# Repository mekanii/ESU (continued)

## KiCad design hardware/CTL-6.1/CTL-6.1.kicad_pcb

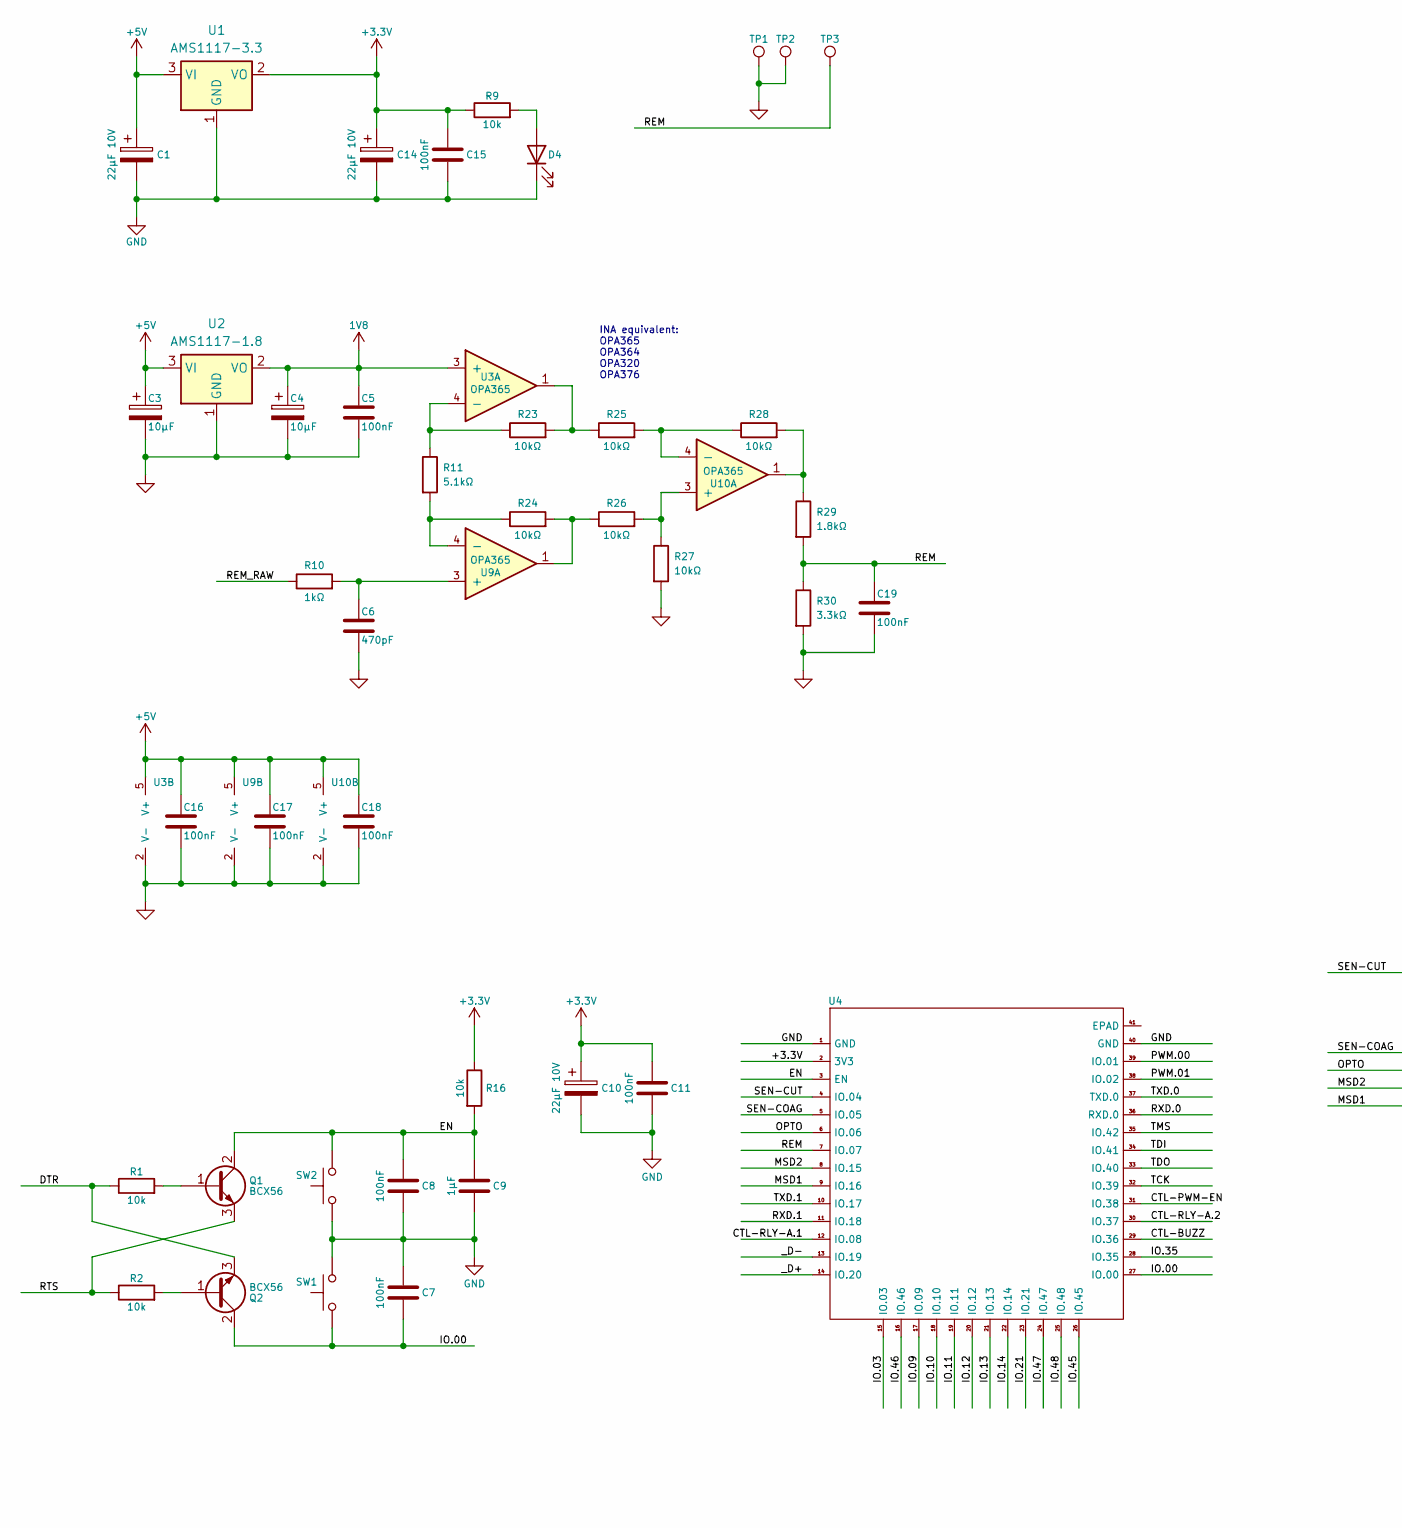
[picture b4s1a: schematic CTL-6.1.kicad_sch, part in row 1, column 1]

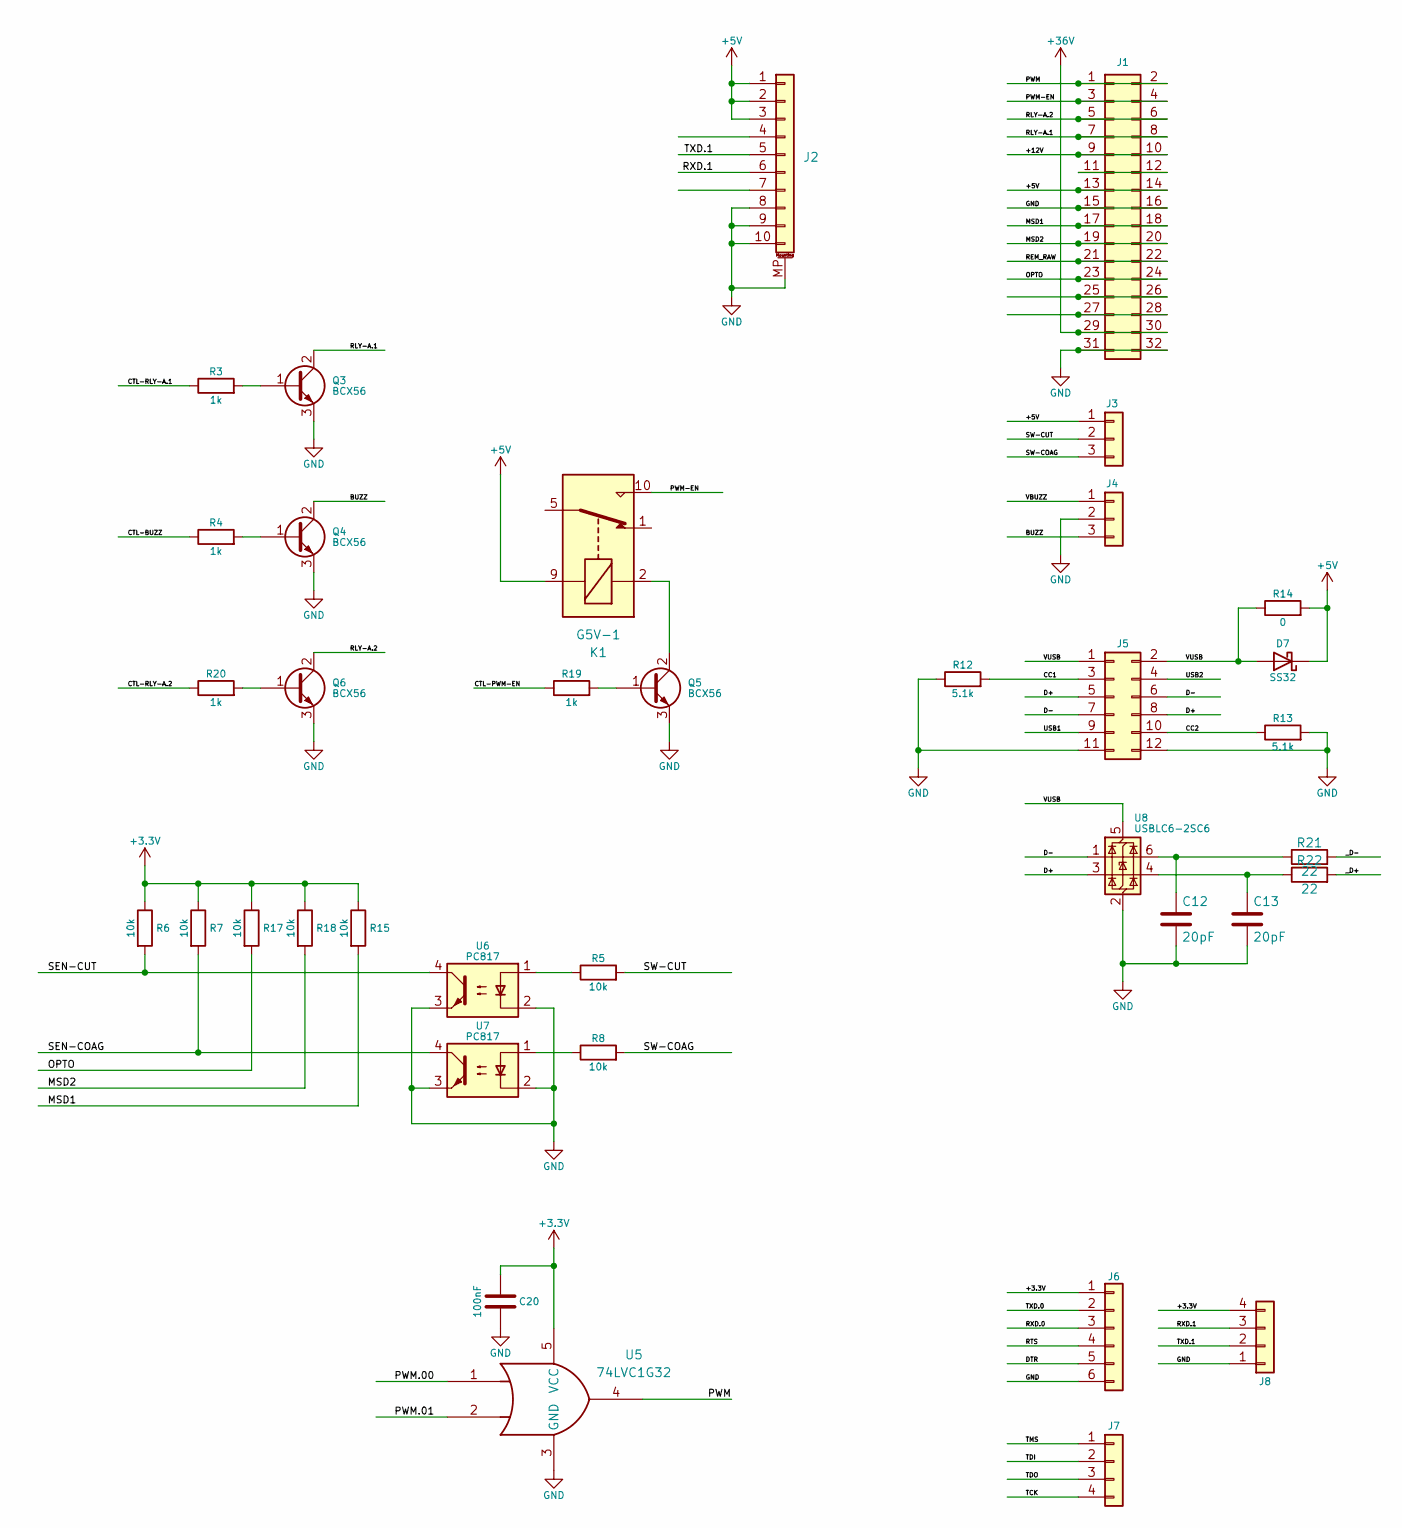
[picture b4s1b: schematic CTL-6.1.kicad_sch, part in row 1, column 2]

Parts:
C1, C10, C14: 22µF 10V; CP_EIA-3216-18_Kemet-A_Pad1.58x1.35mm_HandSolder
C3, C4: 10µF; CP_EIA-3216-18_Kemet-A_Pad1.58x1.35mm_HandSolder
C5, C7, C8, C11, C15, C16, C17, C18, C19, C20: 100nF; C_0805_2012Metric_Pad1.18x1.45mm_HandSolder
C6: 470pF; C_0805_2012Metric_Pad1.18x1.45mm_HandSolder
C9: 1µF; C_0805_2012Metric_Pad1.18x1.45mm_HandSolder
C12, C13: 20pF; C_0805_2012Metric_Pad1.18x1.45mm_HandSolder
D4: LED; LED_0805_2012Metric_Pad1.15x1.40mm_HandSolder
D7: SS32; D_SMA
J1: Conn_02x16_Top_Bottom; PinHeader_2x16_P2.54mm_Horizontal_NoPins
J2: TE_1-84952-0_1x10-1MP_P1.0mm_Horizontal
J3, J4: Conn_01x03; JST_XH_B3B-XH-A_1x03_P2.50mm_Vertical
J5: Conn_02x06_Odd_Even; PinHeader_2x06_P2.54mm_Vertical
J6: Conn_01x04; PinHeader_1x06_P2.54mm_Vertical
J7, J8: Conn_01x04; PinHeader_1x04_P2.54mm_Vertical
K1: G5V-1; Relay_SPDT_Omron_G5V-1
Q1, Q2, Q3, Q4, Q5, Q6: BCX56; SOT-89-3
R1, R2, R5, R6, R7, R8, R9, R15, R16, R17, R18: 10k; R_0805_2012Metric_Pad1.20x1.40mm_HandSolder
R3, R4, R19, R20: 1k; R_0805_2012Metric_Pad1.20x1.40mm_HandSolder
R10: 1kΩ; R_0805_2012Metric_Pad1.20x1.40mm_HandSolder
R11: 5.1kΩ; R_0805_2012Metric_Pad1.20x1.40mm_HandSolder
R12, R13: 5.1k; R_0805_2012Metric_Pad1.20x1.40mm_HandSolder
R14: 0; R_1206_3216Metric_Pad1.30x1.75mm_HandSolder
R21, R22: 22; R_0805_2012Metric_Pad1.20x1.40mm_HandSolder
R23, R24, R25, R26, R27, R28: 10kΩ; R_0805_2012Metric_Pad1.20x1.40mm_HandSolder
R29: 1.8kΩ; R_0805_2012Metric_Pad1.20x1.40mm_HandSolder
R30: 3.3kΩ; R_0805_2012Metric_Pad1.20x1.40mm_HandSolder
SW1, SW2: SW_Omron_B3FS; SW_SPST_Omron_B3FS-100xP
TP1, TP2, TP3: TestPoint; TestPoint_Bridge_Pitch2.54mm_Drill1.0mm
U1: AMS1117-3.3; SOT-223-3_TabPin2
U2: AMS1117-1.8; SOT-223-3_TabPin2
U3, U9, U10: OPA365; SOT-23-5_HandSoldering
U4: ESP32-S3-WROOM-1U
U5: 74LVC1G32; SOT-23-5_HandSoldering
U6, U7: PC817; DIP-4_W7.62mm_Socket
U8: USBLC6-2SC6; SOT-23-6

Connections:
1V8: C4.1, C5.1, U2.2 (VO), U3.3 (+)
+3.3V: C10.1, C11.2, C14.1, C15.2, C20.2, J6.1, J8.4, R6.1, R7.1, R9.1, R15.1, R16.1, R17.1, R18.1, U1.2 (VO), U4.2 (3V3), U5.5 (VCC)
+5V: C1.1, C3.1, C16.1, C17.1, C18.1, D7.1 (K), J1.13, J1.14, J2.1, J2.2, J2.3, J3.1, K1.9, R14.2, U1.3 (VI), U2.3 (VI), U3.5 (V+), U9.5 (V+), U10.5 (V+)
+36V: J1.29, J1.30
/+12V: J1.9, J1.10
/BUZZ: J4.3, Q4.2 (C)
/CC1: J5.3, R12.2
/CC2: J5.10, R13.1
/CTL-BUZZ: R4.1, U4.29 (IO.36)
/CTL-PWM-EN: R19.1, U4.31 (IO.38)
/CTL-RLY-A.1: R3.1, U4.12 (IO.08)
/CTL-RLY-A.2: R20.1, U4.30 (IO.37)
/D+: J5.5, J5.8, U8.3 (I/O2)
/D-: J5.6, J5.7, U8.1 (I/O1)
/DTR: J6.5, Q2.3 (E), R1.1
/EN: C8.2, C9.2, Q1.2 (C), R16.2, SW2.2, U4.3 (EN)
/IO.00: C7.2, Q2.2 (C), SW1.1, U4.27 (IO.00)
/IO.03: U4.15 (IO.03)
/IO.09: U4.17 (IO.09)
/IO.10: U4.18 (IO.10)
/IO.11: U4.19 (IO.11)
/IO.12: U4.20 (IO.12)
/IO.13: U4.21 (IO.13)
/IO.14: U4.22 (IO.14)
/IO.21: U4.23 (IO.21)
/IO.35: U4.28 (IO.35)
/IO.45: U4.26 (IO.45)
/IO.46: U4.16 (IO.46)
/IO.47: U4.24 (IO.47)
/IO.48: U4.25 (IO.48)
/MSD1: J1.17, J1.18, R15.2, U4.9 (IO.16)
/MSD2: J1.19, J1.20, R18.2, U4.8 (IO.15)
/OPTO: J1.23, J1.24, R17.2, U4.6 (IO.06)
/PWM: J1.1, J1.2, U5.4
/PWM-EN: J1.3, J1.4, K1.10
/PWM.00: U4.39 (IO.01), U5.1
/PWM.01: U4.38 (IO.02), U5.2
/REM: C19.1, R29.2, R30.1, TP3.1 (1_1), U4.7 (IO.07)
/REM_RAW: J1.21, J1.22, R10.1
/RLY-A.1: J1.7, J1.8, Q3.2 (C)
/RLY-A.2: J1.5, J1.6, Q6.2 (C)
/RTS: J6.4, Q1.3 (E), R2.1
/RXD.0: J6.3, U4.36 (RXD.0)
/RXD.1: J2.6, J8.3, U4.11 (IO.18)
/SEN-COAG: R7.2, U4.5 (IO.05), U7.4
/SEN-CUT: R6.2, U4.4 (IO.04), U6.4
/SW-COAG: J3.3, R8.2
/SW-CUT: J3.2, R5.2
/TCK: J7.4, U4.32 (IO.39)
/TDI: J7.2, U4.34 (IO.41)
/TDO: J7.3, U4.33 (IO.40)
/TMS: J7.1, U4.35 (IO.42)
/TXD.0: J6.2, U4.37 (TXD.0)
/TXD.1: J2.5, J8.2, U4.10 (IO.17)
/USB1: J5.9
/USB2: J5.4
/VBUZZ: J4.1
/VUSB: D7.2 (A), J5.1, J5.2, R14.1, U8.5 (VBUS)
/_D+: R22.2, U4.14 (IO.20)
/_D-: R21.2, U4.13 (IO.19)
GND: C1.2, C3.2, C4.2, C5.2, C6.2, C7.1, C8.1, C9.1, C10.2, C11.1, C12.2, C13.2, C14.2, C15.1, C16.2, C17.2, C18.2, C19.2, C20.1, D4.1 (K), J1.15, J1.16, J1.31, J1.32, J2.8, J2.9, J2.10, J2.MP (MountPin), J4.2, J5.11, J5.12, J6.6, J8.1, Q3.3 (E), Q4.3 (E), Q5.3 (E), Q6.3 (E), R12.1, R13.2, R27.2, R30.2, SW1.2, SW2.1, TP1.1 (1_1), TP2.1 (1_1), U1.1 (GND), U2.1 (GND), U3.2 (V-), U4.1 (GND), U4.40 (GND), U5.3 (GND), U6.2, U6.3, U7.2, U7.3, U8.2 (GND), U9.2 (V-), U10.2 (V-)
unnamed: C12.1, R21.1, U8.6 (I/O1)
unnamed: C13.1, R22.1, U8.4 (I/O2)
unnamed: D4.2 (A), R9.2
unnamed: J1.11, J1.12
unnamed: J1.25, J1.26
unnamed: J1.27, J1.28
unnamed: K1.5, K1.6
unnamed: Q1.1 (B), R1.2
unnamed: Q2.1 (B), R2.2
unnamed: Q3.1 (B), R3.2
unnamed: Q4.1 (B), R4.2
unnamed: Q5.1 (B), R19.2
unnamed: K1.2, Q5.2 (C)
unnamed: Q6.1 (B), R20.2
unnamed: R5.1, U6.1
unnamed: R8.1, U7.1
unnamed: R23.2, R25.1, U3.1
unnamed: R24.2, R26.1, U9.1
unnamed: R28.2, R29.1, U10.1
unnamed: R11.1, R23.1, U3.4 (-)
unnamed: C6.1, R10.2, U9.3 (+)
unnamed: R11.2, R24.1, U9.4 (-)
unnamed: R26.2, R27.1, U10.3 (+)
unnamed: R25.2, R28.1, U10.4 (-)

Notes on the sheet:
INA equivalent: OPA365 OPA364 OPA320 OPA376

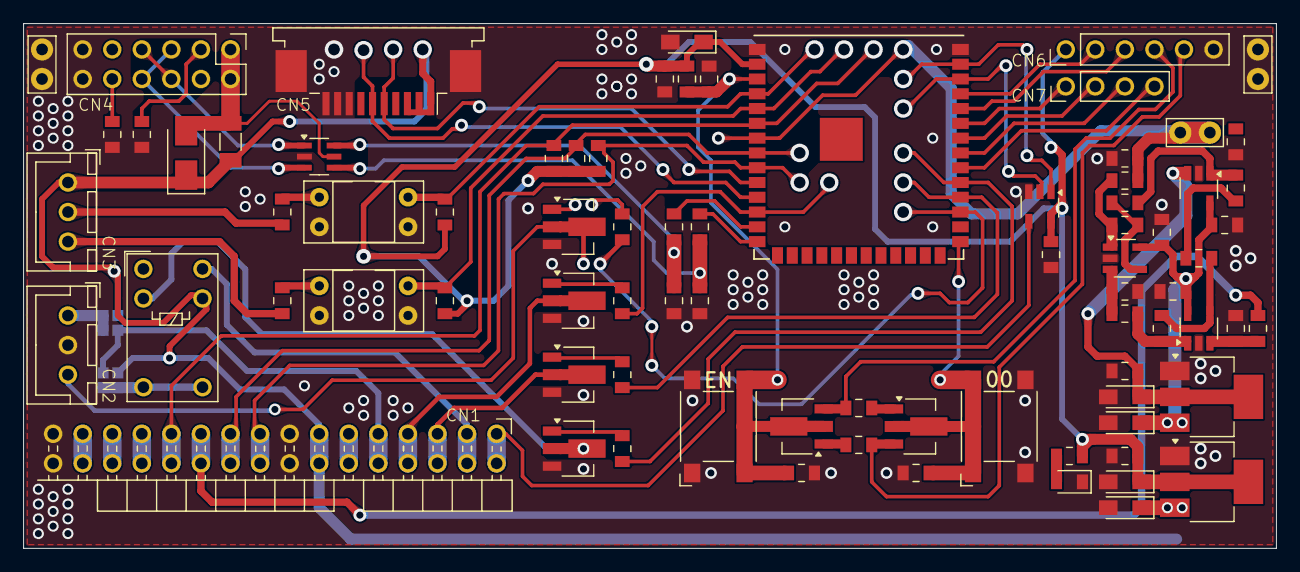
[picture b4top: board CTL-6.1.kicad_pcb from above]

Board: 2 copper layers, 107.6 x 45.1 mm, 80 parts (0 on the bottom side), 69 nets.

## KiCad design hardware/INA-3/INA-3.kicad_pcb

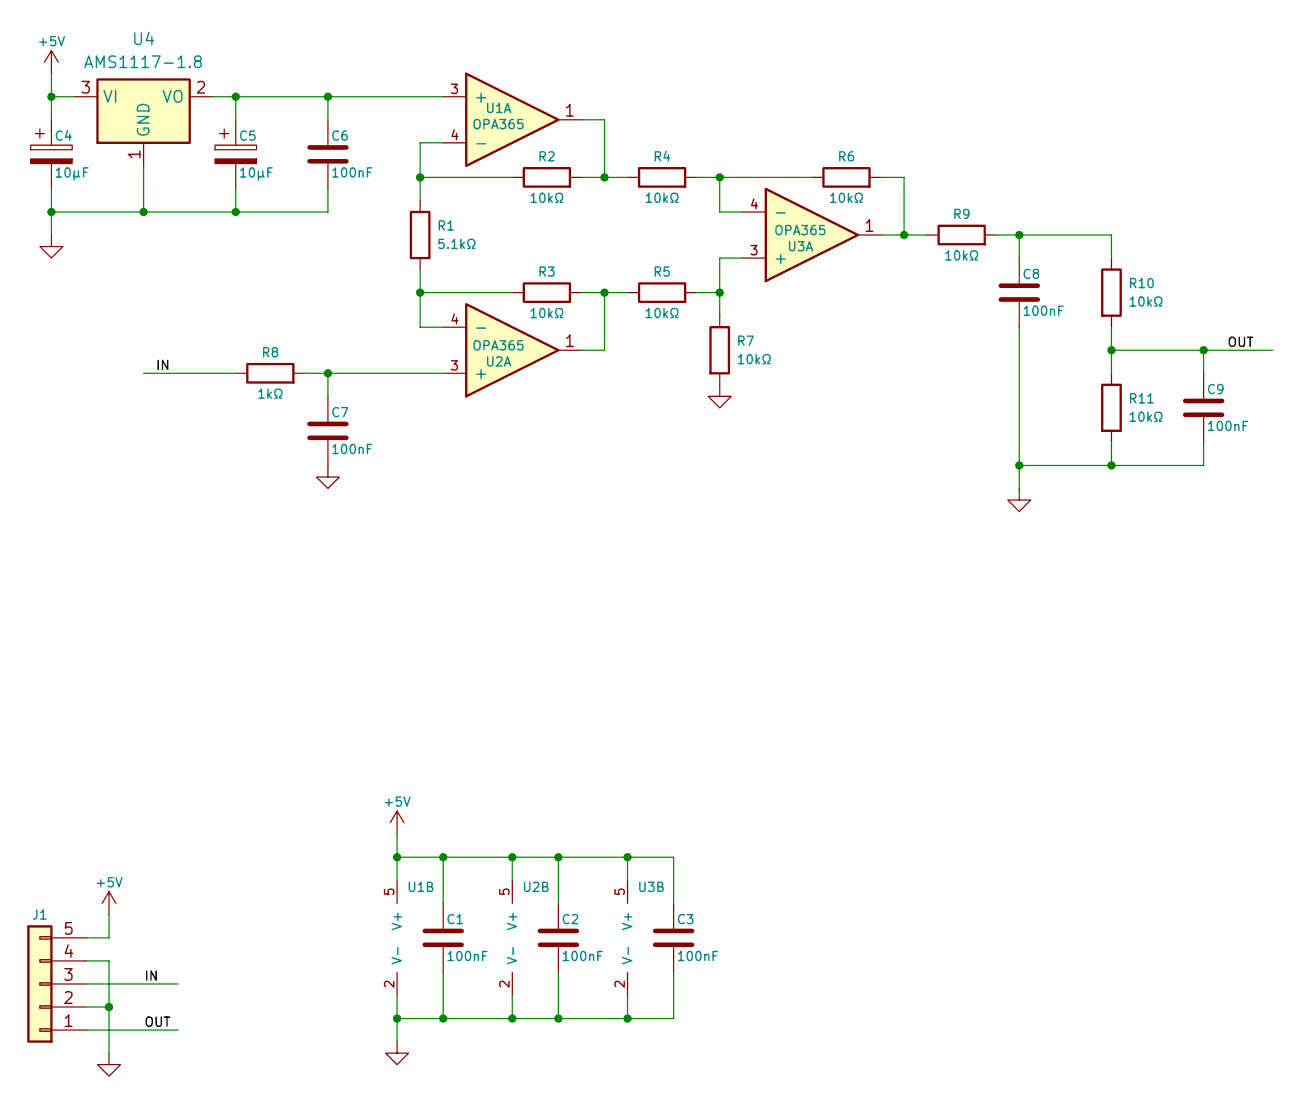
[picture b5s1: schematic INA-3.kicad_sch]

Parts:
C1, C2, C3, C6, C7, C8, C9: 100nF; C_0805_2012Metric_Pad1.18x1.45mm_HandSolder
C4, C5: 10µF; CP_EIA-3528-12_Kemet-T_Pad1.50x2.35mm_HandSolder
J1: Conn_01x05; PinHeader_1x05_P2.54mm_Horizontal_2
R1: 5.1kΩ; R_0805_2012Metric_Pad1.20x1.40mm_HandSolder
R2, R3, R4, R5, R6, R7, R9, R10, R11: 10kΩ; R_0805_2012Metric_Pad1.20x1.40mm_HandSolder
R8: 1kΩ; R_0805_2012Metric_Pad1.20x1.40mm_HandSolder
U1, U2, U3: OPA365; SOT-23-5_HandSoldering
U4: AMS1117-1.8; SOT-223-3_TabPin2

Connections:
+5V: C1.1, C2.1, C3.1, C4.1, J1.5, U1.5 (V+), U2.5 (V+), U3.5 (V+), U4.3 (VI)
/IN: J1.3, R8.1
/OUT: C9.1, J1.1, R10.2, R11.1
GND: C1.2, C2.2, C3.2, C4.2, C5.2, C6.2, C7.2, C8.2, C9.2, J1.2, J1.4, R7.2, R11.2, U1.2 (V-), U2.2 (V-), U3.2 (V-), U4.1 (GND)
unnamed: C8.1, R9.2, R10.1
unnamed: R2.2, R4.1, U1.1
unnamed: R3.2, R5.1, U2.1
unnamed: R6.2, R9.1, U3.1
unnamed: C5.1, C6.1, U1.3 (+), U4.2 (VO)
unnamed: R1.1, R2.1, U1.4 (-)
unnamed: C7.1, R8.2, U2.3 (+)
unnamed: R1.2, R3.1, U2.4 (-)
unnamed: R5.2, R7.1, U3.3 (+)
unnamed: R4.2, R6.1, U3.4 (-)

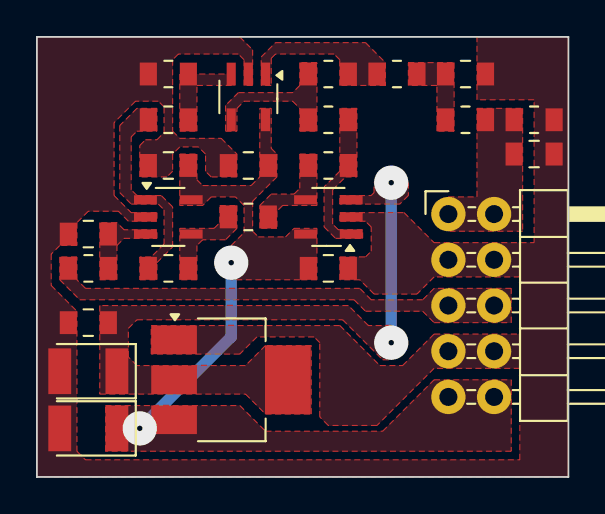
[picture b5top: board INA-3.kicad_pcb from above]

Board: 2 copper layers, 29.5 x 24.4 mm, 25 parts (0 on the bottom side), 14 nets.

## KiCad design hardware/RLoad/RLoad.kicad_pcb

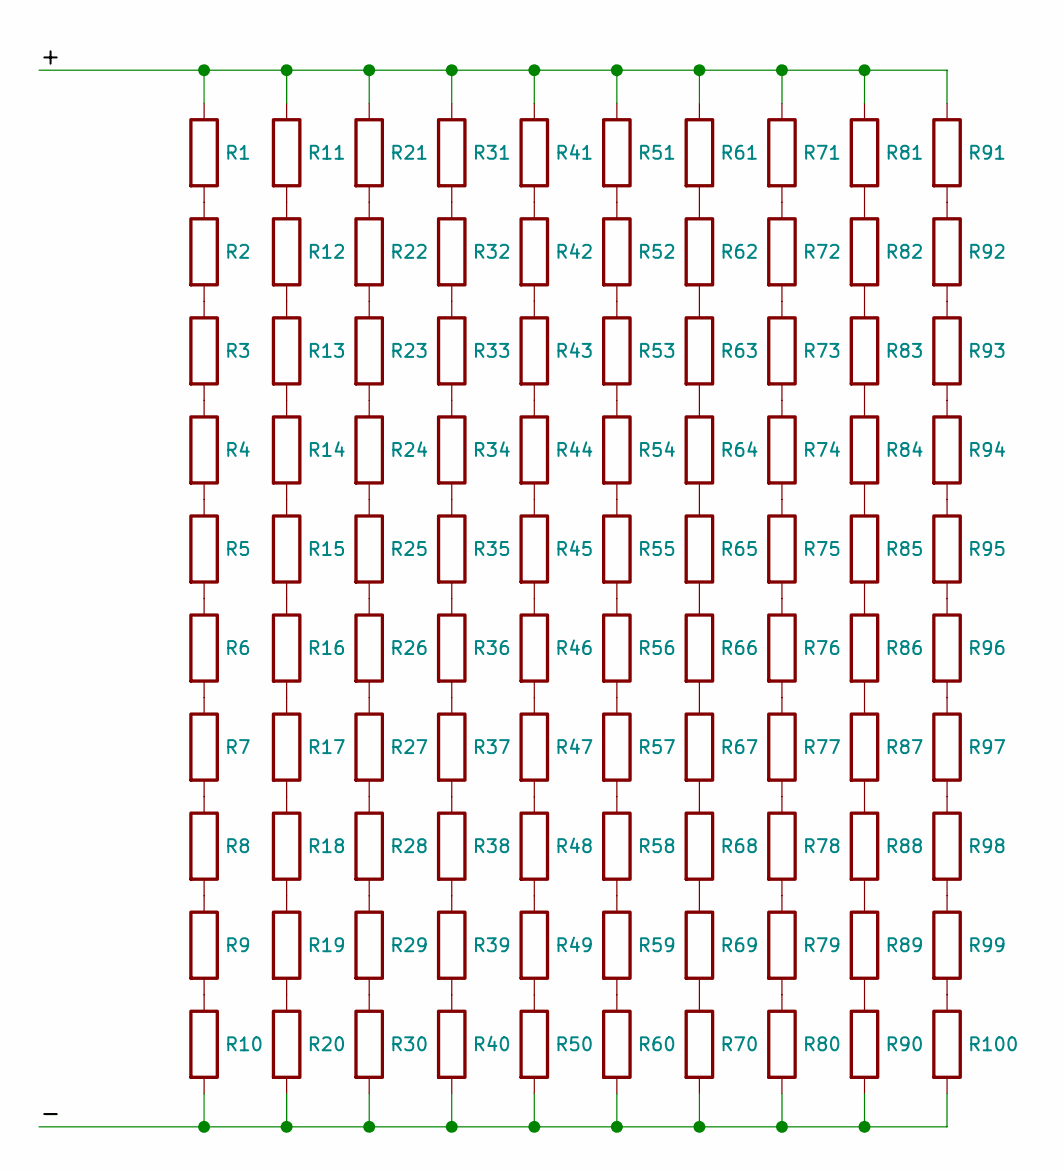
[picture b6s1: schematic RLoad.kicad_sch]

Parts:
R1, R2, R3, R4, R5, R6, R7, R8, R9, R10, R11, R12, R13, R14, R15, R16, R17, R18, R19, R20, R21, R22, R23, R24, R25, R26, R27, R28, R29, R30, R31, R32, R33, R34, R35, R36, R37, R38, R39, R40, R41, R42, R43, R44, R45, R46, R47, R48, R49, R50, R51, R52, R53, R54, R55, R56, R57, R58, R59, R60, R61, R62, R63, R64, R65, R66, R67, R68, R69, R70, R71, R72, R73, R74, R75, R76, R77, R78, R79, R80, R81, R82, R83, R84, R85, R86, R87, R88, R89, R90, R91, R92, R93, R94, R95, R96, R97, R98, R99, R100: R; R_Axial_DIN0414_L11.9mm_D4.5mm_P15.24mm_Horizontal

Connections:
/+: R1.1, R11.1, R21.1, R31.1, R41.1, R51.1, R61.1, R71.1, R81.1, R91.1
/-: R10.2, R20.2, R30.2, R40.2, R50.2, R60.2, R70.2, R80.2, R90.2, R100.2
unnamed: R1.2, R2.1
unnamed: R2.2, R3.1
unnamed: R3.2, R4.1
unnamed: R4.2, R5.1
unnamed: R5.2, R6.1
unnamed: R6.2, R7.1
unnamed: R7.2, R8.1
unnamed: R8.2, R9.1
unnamed: R9.2, R10.1
unnamed: R11.2, R12.1
unnamed: R12.2, R13.1
unnamed: R13.2, R14.1
unnamed: R14.2, R15.1
unnamed: R15.2, R16.1
unnamed: R16.2, R17.1
unnamed: R17.2, R18.1
unnamed: R18.2, R19.1
unnamed: R19.2, R20.1
unnamed: R21.2, R22.1
unnamed: R22.2, R23.1
unnamed: R23.2, R24.1
unnamed: R24.2, R25.1
unnamed: R25.2, R26.1
unnamed: R26.2, R27.1
unnamed: R27.2, R28.1
unnamed: R28.2, R29.1
unnamed: R29.2, R30.1
unnamed: R31.2, R32.1
unnamed: R32.2, R33.1
unnamed: R33.2, R34.1
unnamed: R34.2, R35.1
unnamed: R35.2, R36.1
unnamed: R36.2, R37.1
unnamed: R37.2, R38.1
unnamed: R38.2, R39.1
unnamed: R39.2, R40.1
unnamed: R41.2, R42.1
unnamed: R42.2, R43.1
unnamed: R43.2, R44.1
unnamed: R44.2, R45.1
unnamed: R45.2, R46.1
unnamed: R46.2, R47.1
unnamed: R47.2, R48.1
unnamed: R48.2, R49.1
unnamed: R49.2, R50.1
unnamed: R51.2, R52.1
unnamed: R52.2, R53.1
unnamed: R53.2, R54.1
unnamed: R54.2, R55.1
unnamed: R55.2, R56.1
unnamed: R56.2, R57.1
unnamed: R57.2, R58.1
unnamed: R58.2, R59.1
unnamed: R59.2, R60.1
unnamed: R61.2, R62.1
unnamed: R62.2, R63.1
unnamed: R63.2, R64.1
unnamed: R64.2, R65.1
unnamed: R65.2, R66.1
unnamed: R66.2, R67.1
unnamed: R67.2, R68.1
unnamed: R68.2, R69.1
unnamed: R69.2, R70.1
unnamed: R71.2, R72.1
unnamed: R72.2, R73.1
unnamed: R73.2, R74.1
unnamed: R74.2, R75.1
unnamed: R75.2, R76.1
unnamed: R76.2, R77.1
unnamed: R77.2, R78.1
unnamed: R78.2, R79.1
unnamed: R79.2, R80.1
unnamed: R81.2, R82.1
unnamed: R82.2, R83.1
unnamed: R83.2, R84.1
unnamed: R84.2, R85.1
unnamed: R85.2, R86.1
unnamed: R86.2, R87.1
unnamed: R87.2, R88.1
unnamed: R88.2, R89.1
unnamed: R89.2, R90.1
unnamed: R91.2, R92.1
unnamed: R92.2, R93.1
unnamed: R93.2, R94.1
unnamed: R94.2, R95.1
unnamed: R95.2, R96.1
unnamed: R96.2, R97.1
unnamed: R97.2, R98.1
unnamed: R98.2, R99.1
unnamed: R99.2, R100.1

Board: 2 copper layers, 100 parts (0 on the bottom side), 92 nets, no tracks yet.

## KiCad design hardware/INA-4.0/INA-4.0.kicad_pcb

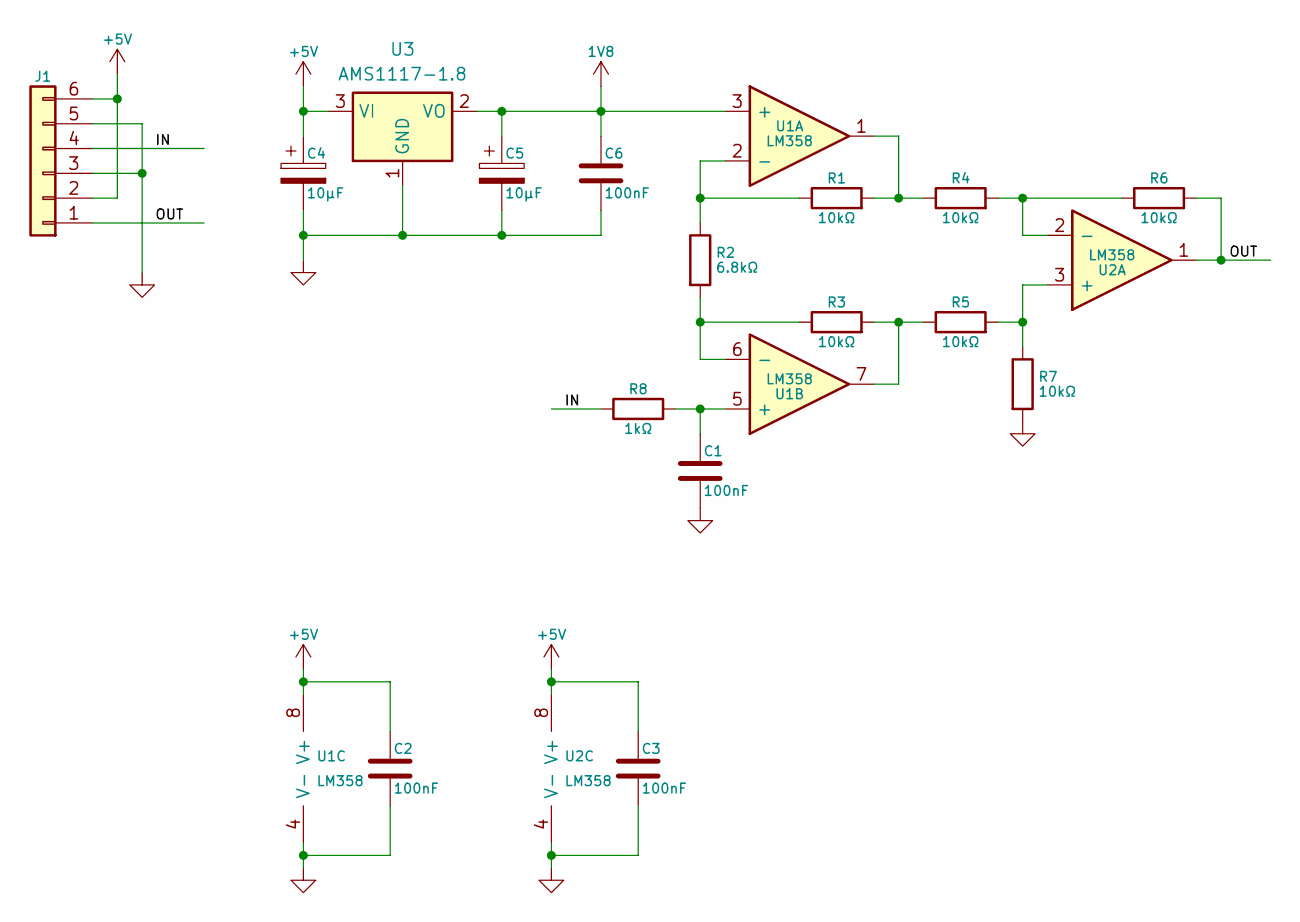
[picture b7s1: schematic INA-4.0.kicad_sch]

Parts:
C1, C2, C3: 100nF; C_Rect_L7.2mm_W2.5mm_P5.00mm_FKS2_FKP2_MKS2_MKP2
C4, C5: 10µF; CP_EIA-3528-12_Kemet-T_Pad1.50x2.35mm_HandSolder
C6: 100nF; C_0805_2012Metric_Pad1.18x1.45mm_HandSolder
J1: Conn_01x05; PinHeader_1x06_P2.54mm_Horizontal
R1, R3, R4, R5, R6, R7: 10kΩ; R_Axial_DIN0204_L3.6mm_D1.6mm_P5.08mm_Horizontal
R2: 6.8kΩ; R_Axial_DIN0204_L3.6mm_D1.6mm_P5.08mm_Horizontal
R8: 1kΩ; R_Axial_DIN0204_L3.6mm_D1.6mm_P5.08mm_Horizontal
U1, U2: LM358; DIP-8_W7.62mm_Socket
U3: AMS1117-1.8; SOT-223-3_TabPin2

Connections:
1V8: C5.1, C6.1, U1.3 (+), U3.2 (VO)
+5V: C2.1, C3.1, C4.1, J1.2, J1.6, U1.8 (V+), U2.8 (V+), U3.3 (VI)
/IN: J1.4, R8.1
/OUT: J1.1, R6.2, U2.1
GND: C1.2, C2.2, C3.2, C4.2, C5.2, C6.2, J1.3, J1.5, R7.2, U1.4 (V-), U2.4 (V-), U3.1 (GND)
unnamed: R1.2, R4.1, U1.1
unnamed: R3.2, R5.1, U1.7
unnamed: R1.1, R2.1, U1.2 (-)
unnamed: C1.1, R8.2, U1.5 (+)
unnamed: R2.2, R3.1, U1.6 (-)
unnamed: R5.2, R7.1, U2.3 (+)
unnamed: R4.2, R6.1, U2.2 (-)

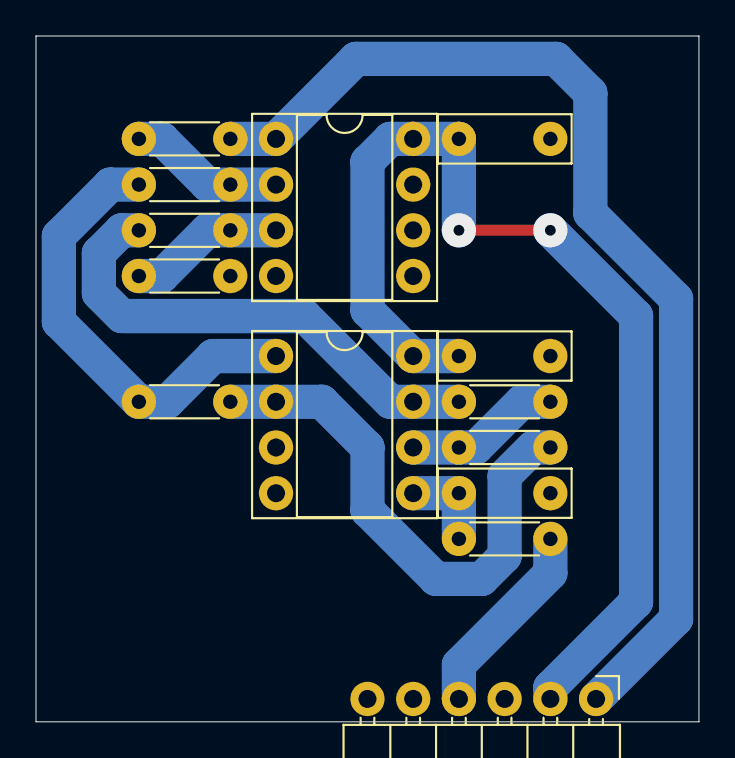
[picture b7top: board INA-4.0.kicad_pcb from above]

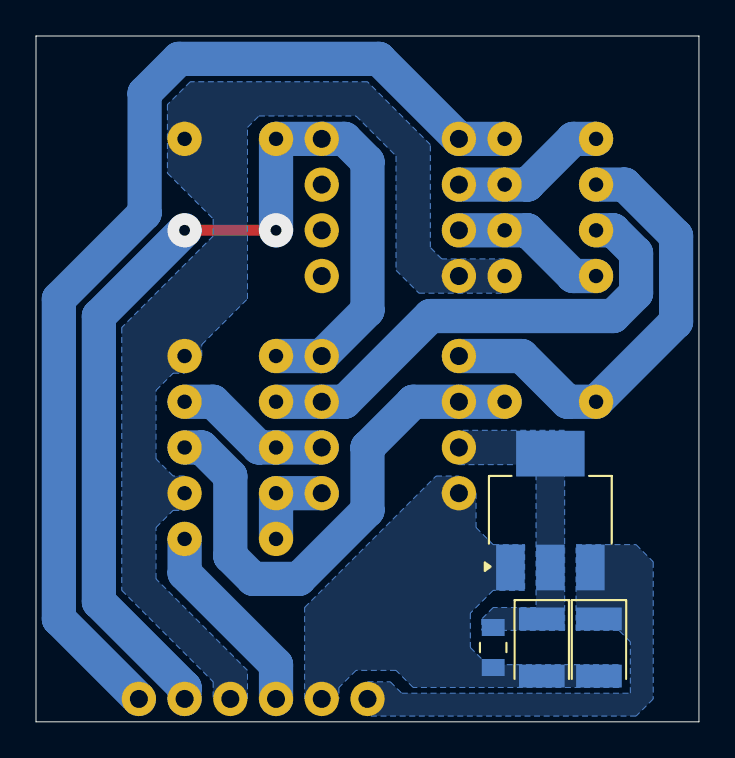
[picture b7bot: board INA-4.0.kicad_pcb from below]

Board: 2 copper layers, 36.8 x 38.1 mm, 18 parts (4 on the bottom side), 12 nets.

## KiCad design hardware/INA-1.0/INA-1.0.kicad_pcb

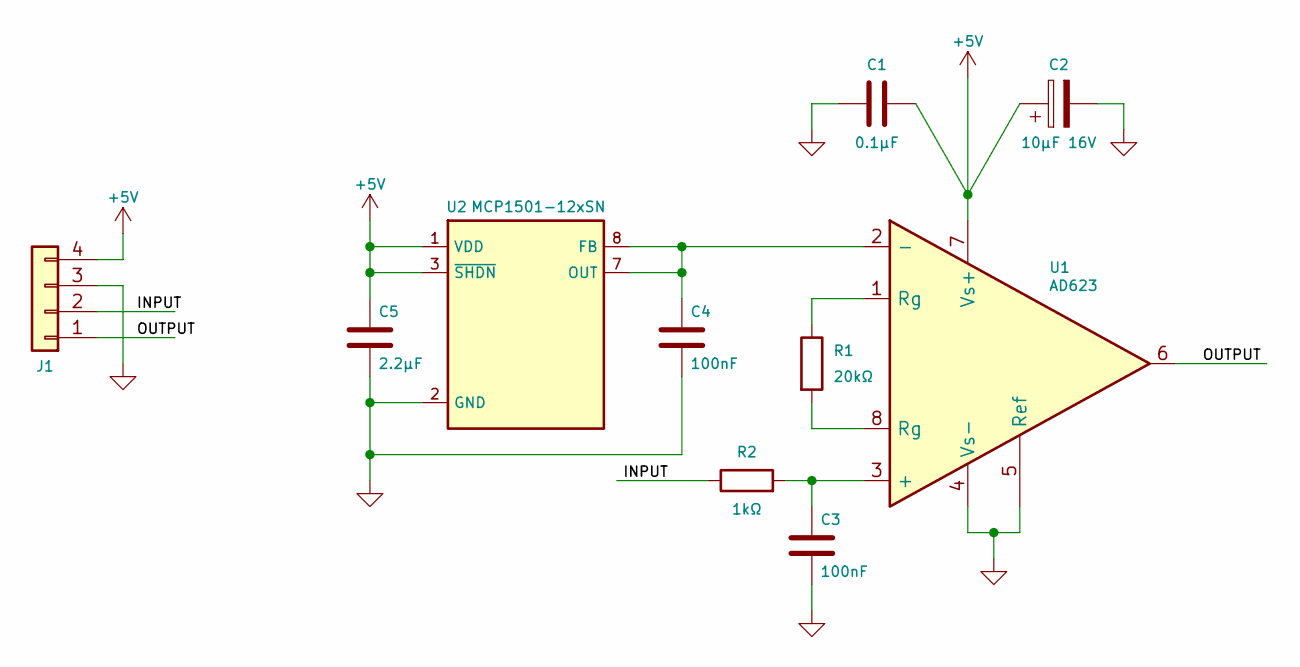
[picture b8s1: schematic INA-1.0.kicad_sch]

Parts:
C1: 0.1µF; C_0805_2012Metric_Pad1.18x1.45mm_HandSolder
C2: 10µF 16V; CP_EIA-3528-12_Kemet-T_Pad1.50x2.35mm_HandSolder
C3, C4: 100nF; C_0805_2012Metric_Pad1.18x1.45mm_HandSolder
C5: 2.2µF; C_0805_2012Metric_Pad1.18x1.45mm_HandSolder
J1: Conn_01x04; PinHeader_1x04_P2.54mm_Horizontal_2
R1: 20kΩ; R_0805_2012Metric_Pad1.20x1.40mm_HandSolder
R2: 1kΩ; R_0805_2012Metric_Pad1.20x1.40mm_HandSolder
U1: AD623; DIP-8_W7.62mm_SMDSocket_SmallPads
U2: MCP1501-12xSN; SOIC-8_3.9x4.9mm_P1.27mm

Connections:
+5V: C1.1, C2.1, C5.1, J1.4, U1.7 (Vs+), U2.1 (VDD), U2.3 (~SHDN)
/INPUT: J1.2, R2.1
/OUTPUT: J1.1, U1.6
GND: C1.2, C2.2, C3.2, C4.2, C5.2, J1.3, U1.4 (Vs-), U1.5 (Ref), U2.2 (GND), U2.4 (GND), U2.5 (GND), U2.6 (GND)
unnamed: R1.1, U1.1 (Rg)
unnamed: R1.2, U1.8 (Rg)
unnamed: C3.1, R2.2, U1.3 (+)
unnamed: C4.1, U1.2 (-), U2.7 (OUT), U2.8 (FB)

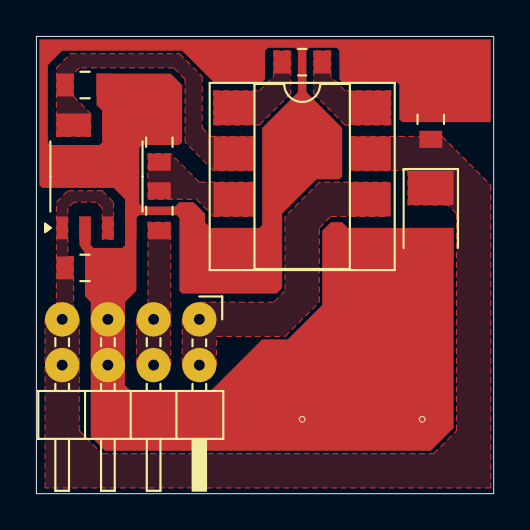
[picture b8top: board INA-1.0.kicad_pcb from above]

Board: 2 copper layers, 25.4 x 25.4 mm, 10 parts (0 on the bottom side), 8 nets.

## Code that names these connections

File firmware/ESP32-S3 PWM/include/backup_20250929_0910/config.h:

#ifndef CONFIG_H
#define CONFIG_H

#include <Arduino.h>
#include <driver/rmt.h>
#include <driver/adc.h>

// RMT Channel definitions
#define RMT_TX_CHANNEL_0  RMT_CHANNEL_0
#define RMT_TX_CHANNEL_1  RMT_CHANNEL_1

// Pin definitions
#define SENS_CUT          4
#define SENS_COAG         5
#define OPTO              6
#define REM               7
#define REM_UPPER_LIMIT   694
#define MSD1              16
#define MSD2              15
#define CTL_RLY_1         8
#define CTL_RLY_2         37
#define CTL_PWM_EN        38
#define CTL_BUZZ          36

// ADC configuration
#define ADC_CHANNEL       ADC1_CHANNEL_6
#define ADC_WIDTH         ADC_WIDTH_BIT_12
#define ADC_ATTEN         ADC_ATTEN_DB_12

// LittleFS configuration
#define FORMAT_LITTLEFS_IF_FAILED true

// Data management configuration
#define MAX_DATA_SETS 10
#define JSON_DOC_SIZE 2048
#define JSON_DATA_FILE "/data.json"

// Display Properties
#define SP80_90_A0_DEFAULT_X 210
#define SP80_90_A0_DEFAULT_Y 125

#define SPB0_C0_D0_DEFAULT_X 660
#define SPB0_C0_D0_DEFAULT_Y 125

#define KEY_CANCEL  0x00F0

// PWM configuration
const gpio_num_t PWM_0 = (gpio_num_t)1;
const gpio_num_t PWM_1 = (gpio_num_t)2;

// Button debounce configuration
const unsigned long debounceDelay = 50; // 50ms debounce delay

#endif // CONFIG_H

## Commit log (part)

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2025-08-12 new file: hardware/PS-2.0/#auto_saved_files# deleted: hardware/PS-2.0/PS-2.0-backups/PS-2.0-2025-08-01_150036.zip deleted: hardware/PS-2.0/PS-2.0-backups/PS-2.0-2025-08-01_151758.zip deleted: hardwar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
2025-08-12 modified: README.md
2025-08-13 modified: .DS_Store modified: README.md modified: pic/.DS_Store renamed: pic/PS/400kHz/1/LC-29u-3n3/comparison.drawio -> pic/PS/400kHz/1/comparison.drawio new file: pic/PS/400kHz/2/400kHz-2-compariso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
2025-08-14 modified: README.md modified: pic/PS/400kHz/1/400kHz-1-analysis.png modified: pic/PS/400kHz/1/analysis.drawio modified: pic/PS/400kHz/1/frequency-variation-across-discrete-levels.png new file: pic/PS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
2025-08-14 modified: README.md new file: pic/PS/25kHz/25kHz-comparison.png modified: pic/PS/25kHz/comparison.drawio
2025-08-25 modified: Ferrite Transformer Calculation.xlsx modified: README.md modified: pic/PWM.drawio
2025-08-25 modified: .DS_Store modified: README.md new file: hardware/CTL-4.0/CTL-4.0-backups/CTL-4.0-2025-08-25_142141.zip deleted: hardware/CTL-4.0/~CTL-4.0.kicad_sch.lck
2025-08-26 modified: .DS_Store modified: README.md modified: log.md
2025-08-29 modified: .DS_Store modified: pic/PS/400kHz/1/R-500-LC-29u-1n/10.png modified: pic/PS/400kHz/1/R-500-LC-29u-1n/100.png modified: pic/PS/400kHz/1/R-500-LC-29u-1n/20.png modified: pic/PS/400kHz/1/R-500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
2025-09-04 modified: README.md new file: hardware/CTL-4.0/CTL-4.0-backups/CTL-4.0-2025-09-04_103940.zip modified: pic/UI/DWIN.drawio
2025-09-07 modified: README.mdw
2025-09-08 new file: ui/image/00_background.png
2025-09-08 new file: ui/0_DWIN_ASC.HZK new file: ui/DWIN_SET/00_background.png new file: ui/DWIN_SET/0_DWIN_ASC.HZK new file: ui/DWIN_SET/32_background.icl modified: ui/DWprj.hmi new file: ui/TFT/00_background.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
2025-09-08 modified: ui/DWIN_SET/T5LCFG.CFG
2025-09-09 modified: pic/UI/DWIN.drawio modified: ui/image/00_background.png new file: ui/image/01_background.png new file: ui/image/02_background.png new file: ui/image/03_background.png new file: ui/image/04_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
2025-09-09 modified: pic/UI/DWIN.drawio modified: ui/image/06_background.png modified: ui/image/07_background.png modified: ui/image/08_background.png
2025-09-09 modified: .gitignore modified: pic/UI/DWIN.drawio
2025-09-09 modified: ui/DWIN_SET/14ShowFile.bin modified: ui/TFT/00_background.png.tft modified: ui/TFT/01_background.png.tft modified: ui/TFT/02_background.png.tft modified: ui/TFT/03_background.png.tft modifi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
2025-09-09 modified: ui/DWIN_SET/13TouchFile.bin modified: ui/DWIN_SET/14ShowFile.bin modified: ui/TFT/00_background.png.tft modified: ui/TFT/01_background.png.tft modified: ui/TFT/02_background.png.tft modifie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
2025-09-10 modified: ui/0_DWIN_ASC.HZK modified: ui/DWIN_SET/0_DWIN_ASC.HZK modified: ui/TFT/00_background.png.tft
2025-09-10 modified: ui/ICON/62/0.png modified: ui/ICON/62/1.png modified: ui/ICON/62/2.png modified: ui/ICON/62/3.png modified: ui/ICON/62/4.png modified: ui/ICON/62/5.png modified: ui/ICON/62/6.png modified: 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
2025-09-10 modified: ui/image/32/00.png modified: ui/image/32/01.png modified: ui/image/32/02.png modified: ui/image/32/03.png modified: ui/image/32/04.png modified: ui/image/32/05.png modified: ui/image/32/06.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
2025-09-10 modified: ui/image/32/00.png modified: ui/image/32/01.png modified: ui/image/32/02.png modified: ui/image/32/03.png modified: ui/image/32/04.png modified: ui/image/32/05.png modified: ui/image/32/06.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
2025-09-10 new file: ui/62/0.png new file: ui/62/1.png new file: ui/62/2.png new file: ui/62/3.png new file: ui/62/4.png new file: ui/62/5.png new file: ui/62/6.png new file: ui/62/7.png new file: ui/62/8.png n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
2025-09-11 modified: ui/DWIN_SET/09.png modified: ui/DWIN_SET/10.png modified: ui/DWIN_SET/11.png modified: ui/DWIN_SET/12.png modified: ui/DWIN_SET/13.png modified: ui/DWIN_SET/14.png modified: ui/DWIN_SET/15.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
2025-09-16 new file: ui/image/32/18-SAVE.png new file: ui/image/32/19-SAVE.png new file: ui/image/32/20-LOAD.png new file: ui/image/32/21-LOAD.png
2025-09-17 modified: ui/DWIN_SET/13TouchFile.bin modified: ui/TFT/03.png.tft modified: ui/TFT/04.png.tft modified: ui/TFT/05.png.tft modified: ui/TFT/07.png.tft modified: ui/TFT/08.png.tft modified: ui/TFT/20-L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
2025-09-18 modified: .DS_Store modified: log.md modified: ui/image/32/00.png modified: ui/image/32/01.png modified: ui/image/32/02.png modified: ui/image/32/03.png modified: ui/image/32/04.png modified: ui/imag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
2025-09-18 modified: ui/DWIN_SET/13TouchFile.bin modified: ui/DWIN_SET/14ShowFile.bin modified: ui/TFT/01.bmp.tft modified: ui/TFT/02.bmp.tft modified: ui/TFT/03.bmp.tft modified: ui/TFT/04.bmp.tft modified: ui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
2025-09-19 modified: .DS_Store modified: firmware/ESP32-S3 PWM/include/config.h modified: firmware/ESP32-S3 PWM/include/display_comm.h modified: firmware/ESP32-S3 PWM/src/display_comm.cpp modified: log.md delet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
2025-09-23 modified: ui/DWIN_SET/14ShowFile.bin modified: ui/TFT/00.bmp.tft modified: ui/TFT/01.bmp.tft modified: ui/TFT/02.bmp.tft
2025-09-23 modified: ui/DWIN_SET/13TouchFile.bin modified: ui/DWIN_SET/14ShowFile.bin modified: ui/DisplayConfig.xls modified: ui/TFT/00.bmp.tft modified: ui/TFT/06.bmp.tft modified: ui/TFT/07.bmp.tft modified: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
2025-09-24 new file: ui/DWIN_SET/00.jpg new file: ui/DWIN_SET/01.jpg new file: ui/DWIN_SET/02.jpg new file: ui/DWIN_SET/03.jpg new file: ui/DWIN_SET/04.jpg new file: ui/DWIN_SET/05.jpg new file: ui/DWIN_SET/06.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
2025-09-24 modified: .DS_Store modified: ui/image/32_800_480_SIMPLE/00.jpg modified: ui/image/32_800_480_SIMPLE/01.jpg modified: ui/image/32_800_480_SIMPLE/02.jpg modified: ui/image/32_800_480_SIMPLE/03.jpg mod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
2025-09-24 modified: ui/DWIN_SET/00.jpg modified: ui/DWIN_SET/01.jpg modified: ui/DWIN_SET/02.jpg modified: ui/DWIN_SET/03.jpg modified: ui/DWIN_SET/04.jpg modified: ui/DWIN_SET/05.jpg modified: ui/DWIN_SET/06.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
2025-09-24 new file: ui/image/32_1600_960_SIMPLE/00.jpg new file: ui/image/32_1600_960_SIMPLE/01.jpg new file: ui/image/32_1600_960_SIMPLE/02.jpg new file: ui/image/32_1600_960_SIMPLE/03.jpg new file: ui/image/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
2025-09-24 modified: ui/DWIN_SET/13TouchFile.bin modified: ui/TFT/00.bmp.tft
2025-09-25 modified: ui/DWIN_SET/00.bmp modified: ui/DWIN_SET/01.bmp modified: ui/DWIN_SET/02.bmp modified: ui/DWIN_SET/03.bmp modified: ui/DWIN_SET/04.bmp modified: ui/DWIN_SET/05.bmp modified: ui/DWIN_SET/06.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
2025-09-25 modified: ui/DWIN_SET/13TouchFile.bin modified: ui/TFT/00.bmp.tft modified: ui/TFT/10.bmp.tft modified: ui/TFT/11.bmp.tft
2025-09-25 new file: ui/DWIN_SET/12.bmp modified: ui/DWIN_SET/13TouchFile.bin modified: ui/DWIN_SET/14ShowFile.bin modified: ui/DWIN_SET/22_Config.bin modified: ui/DWIN_SET/32.icl new file: ui/DWIN_SET/46.icl m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
2025-09-25 new file: ui/46/0.jpg new file: ui/46/1.jpg new file: ui/46/2.jpg new file: ui/46/3.jpg new file: ui/46/4.jpg modified: ui/DWIN_SET/14ShowFile.bin modified: ui/TFT/12.bmp.tft
2025-09-25 modified: ui/DWIN_SET/13TouchFile.bin modified: ui/DWIN_SET/14ShowFile.bin modified: ui/TFT/00.bmp.tft modified: ui/TFT/12.bmp.tft
2025-09-25 modified: ui/ICON/46/01.jpg
2025-09-25 modified: ui/DWIN_SET/13TouchFile.bin modified: ui/DWIN_SET/22_Config.bin modified: ui/TFT/00.bmp.tft
2025-09-26 modified: ui/DWIN_SET/13TouchFile.bin modified: ui/DWIN_SET/22_Config.bin modified: ui/DWIN_SET/backup_22_bin/22_Config.bin modified: ui/TFT/10.bmp.tft modified: ui/TFT/11.bmp.tft
2025-09-26 modified: ui/DWIN_SET/22_Config.bin modified: ui/DWIN_SET/backup_22_bin/22_Config.bin
2025-09-26 modified: ui/DWIN_SET/22_Config.bin
2025-09-29 modified: ui/DWIN_SET/13TouchFile.bin modified: ui/DWIN_SET/22_Config.bin modified: ui/TFT/00.bmp.tft modified: ui/TFT/01.bmp.tft modified: ui/TFT/02.bmp.tft modified: ui/TFT/03.bmp.tft modified: ui/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
2025-09-29 modified: ui/DWIN_SET/13TouchFile.bin modified: ui/DWIN_SET/14ShowFile.bin new file: ui/DWIN_SET/backup_20250929_1017/0_DWIN_ASC.HZK new file: ui/DWIN_SET/backup_20250929_1017/13TouchFile.bin new fil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
2025-09-29 modified: ui/DWIN_SET/13TouchFile.bin modified: ui/TFT/11.bmp.tft
2025-09-29 modified: ui/DWIN_SET/32.icl new file: ui/image/32_800_480_SIMPLE/13_ACTIVE_00_0.bmp new file: ui/image/32_800_480_SIMPLE/14_ACTIVE_00_1.bmp new file: ui/image/32_800_480_SIMPLE/15_ACTIVE_01_0.bmp ne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
2025-09-29 modified: firmware/ESP32-S3 PWM/include/display_comm.h modified: firmware/ESP32-S3 PWM/src/display_comm.cpp modified: firmware/ESP32-S3 PWM/src/hardware_control.cpp modified: ui/image/32_1600_960_SIM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
2025-09-30 new file: firmware/ESP32-S3 PWM/include/buzzer.h modified: firmware/ESP32-S3 PWM/include/hardware_control.h new file: firmware/ESP32-S3 PWM/src/buzzer.cpp modified: firmware/ESP32-S3 PWM/src/display_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
2025-10-18 modified: .DS_Store new file: firmware/ESP32-S3 PWM/test/CC-SEPIC-LED.md new file: hardware/CTL-4.0/CTL-4.0-backups/CTL-4.0-2025-10-03_113905.zip deleted: hardware/CTL-4.1/CTL-4.1-backups/CTL-4.1-202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
2026-01-19 modified: .DS_Store modified: archive/Purchase 20260105.xlsx deleted: hardware/CTL-4.2/CTL-4.2-backups/CTL-4.2-2026-01-07_141653.zip deleted: hardware/CTL-4.2/CTL-4.2-backups/CTL-4.2-2026-01-07_14292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
2026-04-06 modified: .DS_Store new file: CAD/FR_TEST.dxf modified: Ferrite Transformer Calculation.xlsx new file: archive/PR_ 0201_2026.docx modified: archive/Purchase 20260105.xlsx new file: archive/Purchase 2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
2026-04-13 deleted: hardware/INA-1.0/#auto_saved_files# deleted: hardware/INA-1.0/INA-1.0-backups/INA-1.0-2026-04-13_105232.zip deleted: hardware/INA-1.0/INA-1.0-backups/INA-1.0-2026-04-13_105845.zip deleted: h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
2026-04-16 deleted: hardware/INA-1.0/INA-1.0-backups/INA-1.0-2026-04-15_103830.zip new file: hardware/INA-1.0/INA-1.0-backups/INA-1.0-2026-04-15_160158.zip new file: hardware/INA-1.0/INA-1.0-backups/INA-1.0-202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
2026-04-23 modified: .DS_Store new file: hardware/INA-3.1/INA-3-backups/INA-3-2026-04-16_161548.zip new file: hardware/INA-3.1/INA-3-backups/INA-3-2026-04-16_162307.zip new file: hardware/INA-3.1/INA-3-backups/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
2026-04-30 modified: .DS_Store new file: archive/Payment 20260424.pdf new file: archive/Purchase 20260424.docx new file: archive/REM_OUTPUT.xlsx modified: firmware/ESP32-S3 PWM/include/config.h modified: firmwa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
2026-05-20 modified: hardware/REM-5.0/fabrication-output/TRACE_BOT.dxf modified: hardware/REM-5.0/fabrication-output/TRACE_TOP.dxf
2026-05-29 modified: .DS_Store new file: hardware/REM-5.0/#auto_saved_files# deleted: hardware/REM-5.0/REM-5.0-backups/REM-5.0-2026-05-12_155759.zip deleted: hardware/REM-5.0/REM-5.0-backups/REM-5.0-2026-05-12_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
2026-06-05 new file: hardware/INA-3.1/INA-3.1-backups/INA-3.1-2026-06-03_154006.zip new file: hardware/INA-3/INA-3-backups/INA-3-2026-06-03_161017.zip new file: hardware/INA-3/INA-3-backups/INA-3-2026-06-03_161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
2026-06-11 modified: firmware/ESU_V1/include/data_manager.h modified: firmware/ESU_V1/include/hardware_control.h modified: firmware/ESU_V1/src/hardware_control.cpp modified: firmware/ESU_V1/src/main.cpp modifie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
2026-06-11 new file: hardware/INA-3/.history modified: hardware/INA-3/INA-3.kicad_pcb modified: hardware/INA-3/INA-3.kicad_prl modified: hardware/INA-3/INA-3.kicad_pro modified: hardware/INA-3/fabrication-outpu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
2026-06-19 modified: firmware/ESU_V1/include/config.h modified: firmware/ESU_V1/src/hardware_control.cpp new file: hardware/REM-4.0/.history new file: hardware/REM-5.0/.history modified: hardware/REM-5.0/REM-5.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
2026-06-19 modified: .gitignore modified: hardware/INA-3/.history (untracked content) modified: hardware/REM-4.0/.history (modified content, untracked content) modified: hardware/REM-5.0/.history (modified cont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
2026-06-25 new file: hardware/REM-6.0/REM-6.op.raw new file: hardware/REM-6.0/REM-6.raw new file: hardware/REM-7.0/REM-7.0.kicad_pcb new file: hardware/REM-7.0/REM-7.0.kicad_prl new file: hardware/REM-7.0/REM-7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
2026-06-29 deleted: hardware/CTL-6.1/~CTL-6.1.kicad_sch.lck new file: hardware/INA-3/INA-3-backups/INA-3-2026-06-12_142043.zip modified: hardware/INA-3/INA-3.kicad_prl new file: hardware/REM-5.0/REM-5.0-backups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
2026-06-29 deleted: hardware/CTL-6.1/~CTL-6.1.kicad_pcb.lck deleted: hardware/CTL-6.1/~CTL-6.1.kicad_pro.lck deleted: hardware/REM-7.0/~REM-7.0.kicad_pcb.lck deleted: hardware/REM-7.0/~REM-7.0.kicad_pro.lck
2026-06-29 deleted: pic/.DS_Store deleted: pic/Graph/.DS_Store deleted: pic/Reverse Engineering/.DS_Store deleted: pic/Reverse Engineering/scope - generator output/.DS_Store
